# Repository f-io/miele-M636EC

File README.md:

# Miele M636EC

Replacement keypad for the Miele M636EC microwave oven.

This layout offers the choice between the original plastic film or tactile switches. <br>
I’ve opted for the plastic film; however, if it fails in the future, you can easily solder in switches as an alternative.

To install, simply replace the old flex cable with regular wires. <br>
The pin header (pin spacing) on the keypad matches that of the MCU board.

## Error Codes

- **E2** = NTC temperature sensor
- **E5** = Temperature (hot air), only applies to convection oven models
- **E6** = Temperature microwave
- **E14** = Air flap does not open in microwave mode
- **E15** or **E** = Temperature error – removable "C"

## Motivation

Miele refused to supply the required spare parts, offering only a replacement microwave instead. <br>
The original keypad is known to fail, but with this guide, you might be able to repair your microwave and reduce electronic waste! <br>

## Images

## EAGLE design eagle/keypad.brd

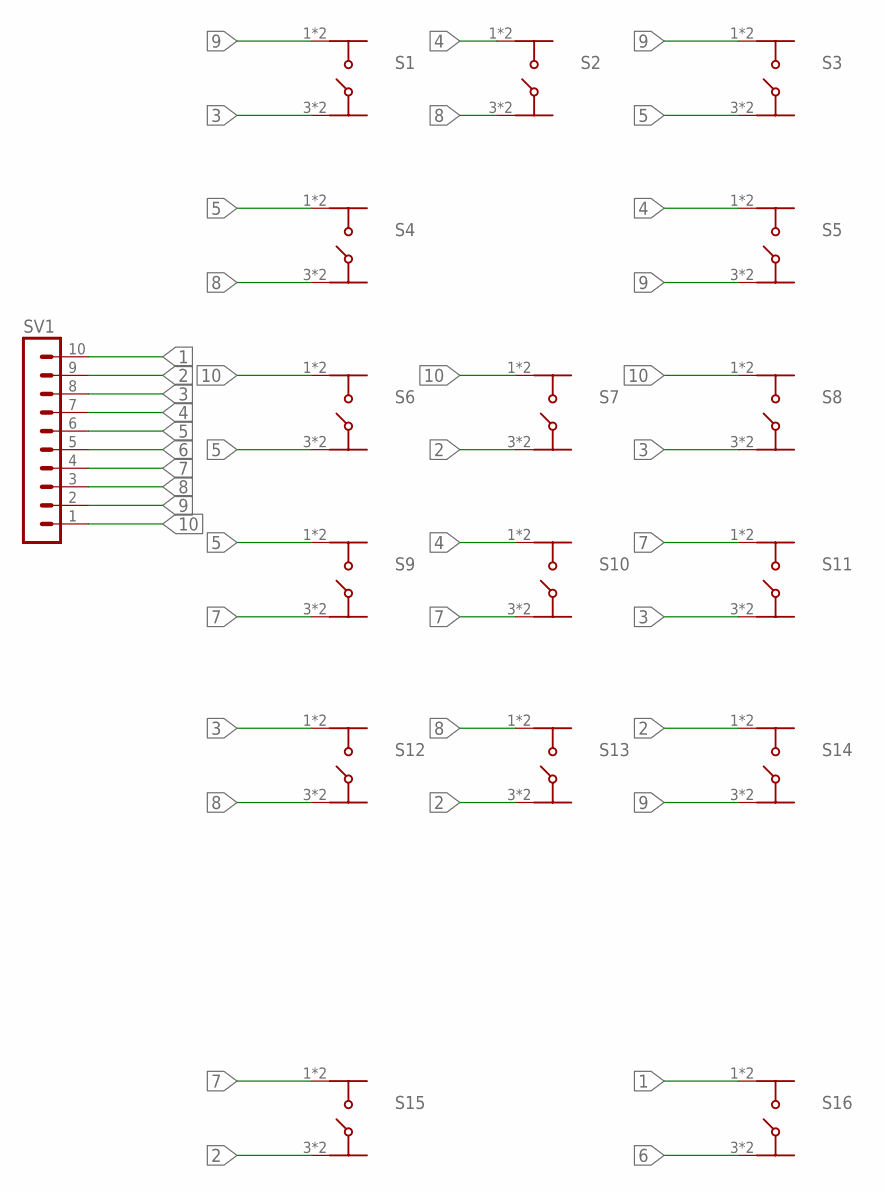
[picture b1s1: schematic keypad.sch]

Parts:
S1, S2, S3, S4, S5, S6, S7, S8, S9, S10, S11, S12, S13, S14, S15, S16: 430481025816
SV1: MA10-1

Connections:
1: S16.1 (A), S16.2 (A), SV1.10
2: S7.3 (B), S7.4 (B), S13.3 (B), S13.4 (B), S14.1 (A), S14.2 (A), S15.3 (B), S15.4 (B), SV1.9
3: S1.3 (B), S1.4 (B), S8.3 (B), S8.4 (B), S11.3 (B), S11.4 (B), S12.1 (A), S12.2 (A), SV1.8
4: S2.1 (A), S2.2 (A), S5.1 (A), S5.2 (A), S10.1 (A), S10.2 (A), SV1.7
5: S3.3 (B), S3.4 (B), S4.1 (A), S4.2 (A), S6.3 (B), S6.4 (B), S9.1 (A), S9.2 (A), SV1.6
6: S16.3 (B), S16.4 (B), SV1.5
7: S9.3 (B), S9.4 (B), S10.3 (B), S10.4 (B), S11.1 (A), S11.2 (A), S15.1 (A), S15.2 (A), SV1.4
8: S2.3 (B), S2.4 (B), S4.3 (B), S4.4 (B), S12.3 (B), S12.4 (B), S13.1 (A), S13.2 (A), SV1.3
9: S1.1 (A), S1.2 (A), S3.1 (A), S3.2 (A), S5.3 (B), S5.4 (B), S14.3 (B), S14.4 (B), SV1.2
10: S6.1 (A), S6.2 (A), S7.1 (A), S7.2 (A), S8.1 (A), S8.2 (A), SV1.1

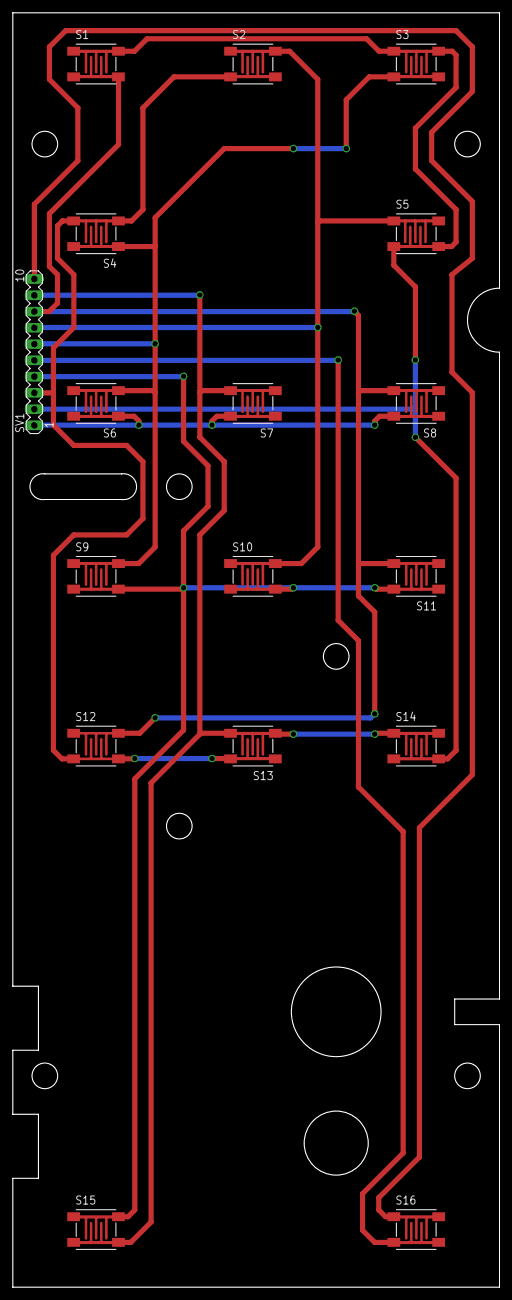
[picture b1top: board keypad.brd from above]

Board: 2 copper layers, 76.0 x 199.0 mm, 17 parts (0 on the bottom side), 10 nets.

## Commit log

2020-12-17 initial release
2020-12-17 add images
2020-12-17 added layout

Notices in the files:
parts and their libraries:
EAGLE-TACT_SWITCHES-rev16e: Copyright: Würth Elektronik
